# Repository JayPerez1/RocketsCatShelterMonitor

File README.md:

# Cat Shelter Monitor

Battery-powered temperature data logger to monitor temperatures and occupency in an outdoor feral cat shelter.

## Hardware (verified)
- Adafruit Feather nRF52840 Express
- DS3231 RTC + CR1220 backup
- 256KB SPI FRAM (CS = A1)
- 2x DS18B20 probes on 1-Wire (DATA = A2, external pull-up installed)
- 1S2P 18650 battery pack (not connected during bench testing)

## Firmware
- v1.0: Logging + BLE UART commands (STATUS / GETNEW / GETALL / CLEAR)

## Docs
- `docs/session-continuity.md`
- `docs/cat-shelter-chat-bootstrap.md`
- `docs/Cat_Shelter_BOM_v4.xlsx`

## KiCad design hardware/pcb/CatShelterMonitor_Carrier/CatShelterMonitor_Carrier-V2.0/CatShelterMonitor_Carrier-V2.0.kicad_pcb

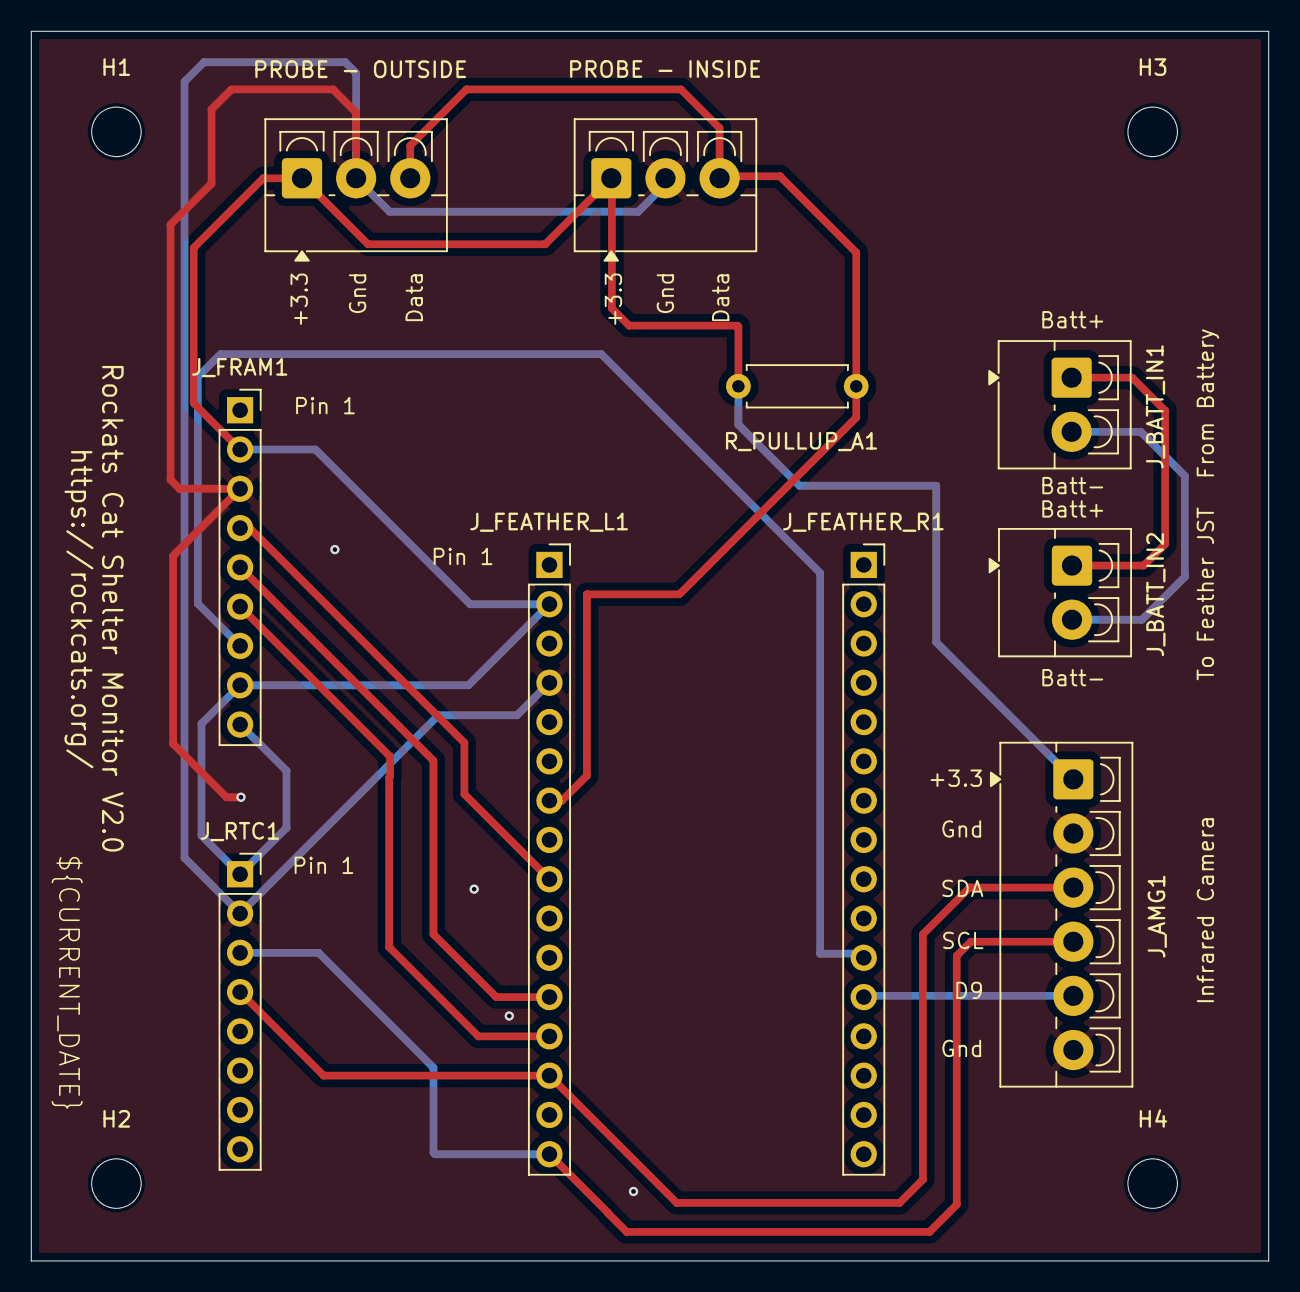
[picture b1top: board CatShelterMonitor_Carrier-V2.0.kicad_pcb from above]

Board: 2 copper layers, 80.0 x 79.5 mm, 14 parts (0 on the bottom side), 12 nets.

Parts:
H1, H2, H3, H4: MountingHole_3.2mm_M3
J_AMG1: TerminalBlock_1x06_P3.5mm; TerminalBlock_4Ucon_1x06_P3.50mm_Vertical
J_BATT_IN1, J_BATT_IN2: J_BATT_OUT; TerminalBlock_4Ucon_1x02_P3.50mm_Vertical
J_FEATHER_L1: Conn_01x16; PinSocket_1x16_P2.54mm_Vertical
J_FEATHER_R1: Conn_01x16; PinSocket_1x16_P2.54mm_Vertical
J_FRAM1: Conn_01x09; PinSocket_1x09_P2.54mm_Vertical
J_RTC1: Conn_01x08; PinSocket_1x08_P2.54mm_Vertical
PROBE - INSIDE: Conn_01x03_Socket; TerminalBlock_4Ucon_1x03_P3.50mm_Vertical
PROBE - OUTSIDE: Conn_01x03_Socket; TerminalBlock_4Ucon_1x03_P3.50mm_Vertical
R_PULLUP_A1: 4.7k; R_Axial_DIN0207_L6.3mm_D2.5mm_P7.62mm_Horizontal

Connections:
+3V3: J_AMG1.1, J_FEATHER_L1.2, J_FRAM1.2, J_FRAM1.8, J_FRAM1.9, J_RTC1.1, PROBE - INSIDE.1, PROBE - OUTSIDE.1, R_PULLUP_A1.2
/A2_1WIRE: J_FEATHER_L1.7, PROBE - INSIDE.3, PROBE - OUTSIDE.3, R_PULLUP_A1.1
/AMG_INT_D9: J_AMG1.5, J_FEATHER_R1.12
/BATT+: J_BATT_IN1.1, J_BATT_IN2.1
/BATT-: J_BATT_IN1.2, J_BATT_IN2.2
/FRAM_CS_D10: J_FEATHER_R1.11, J_FRAM1.7
/I2C_SCL: J_AMG1.4, J_FEATHER_L1.16, J_RTC1.3
/I2C_SDA: J_AMG1.3, J_FEATHER_L1.14, J_RTC1.4
/SPI_MISO: J_FEATHER_L1.12, J_FRAM1.5
/SPI_MOSI: J_FEATHER_L1.13, J_FRAM1.6
/SPI_SCK: J_FEATHER_L1.9, J_FRAM1.4
GND: J_AMG1.2, J_AMG1.6, J_FEATHER_L1.4, J_FRAM1.3, J_RTC1.2, PROBE - INSIDE.2, PROBE - OUTSIDE.2

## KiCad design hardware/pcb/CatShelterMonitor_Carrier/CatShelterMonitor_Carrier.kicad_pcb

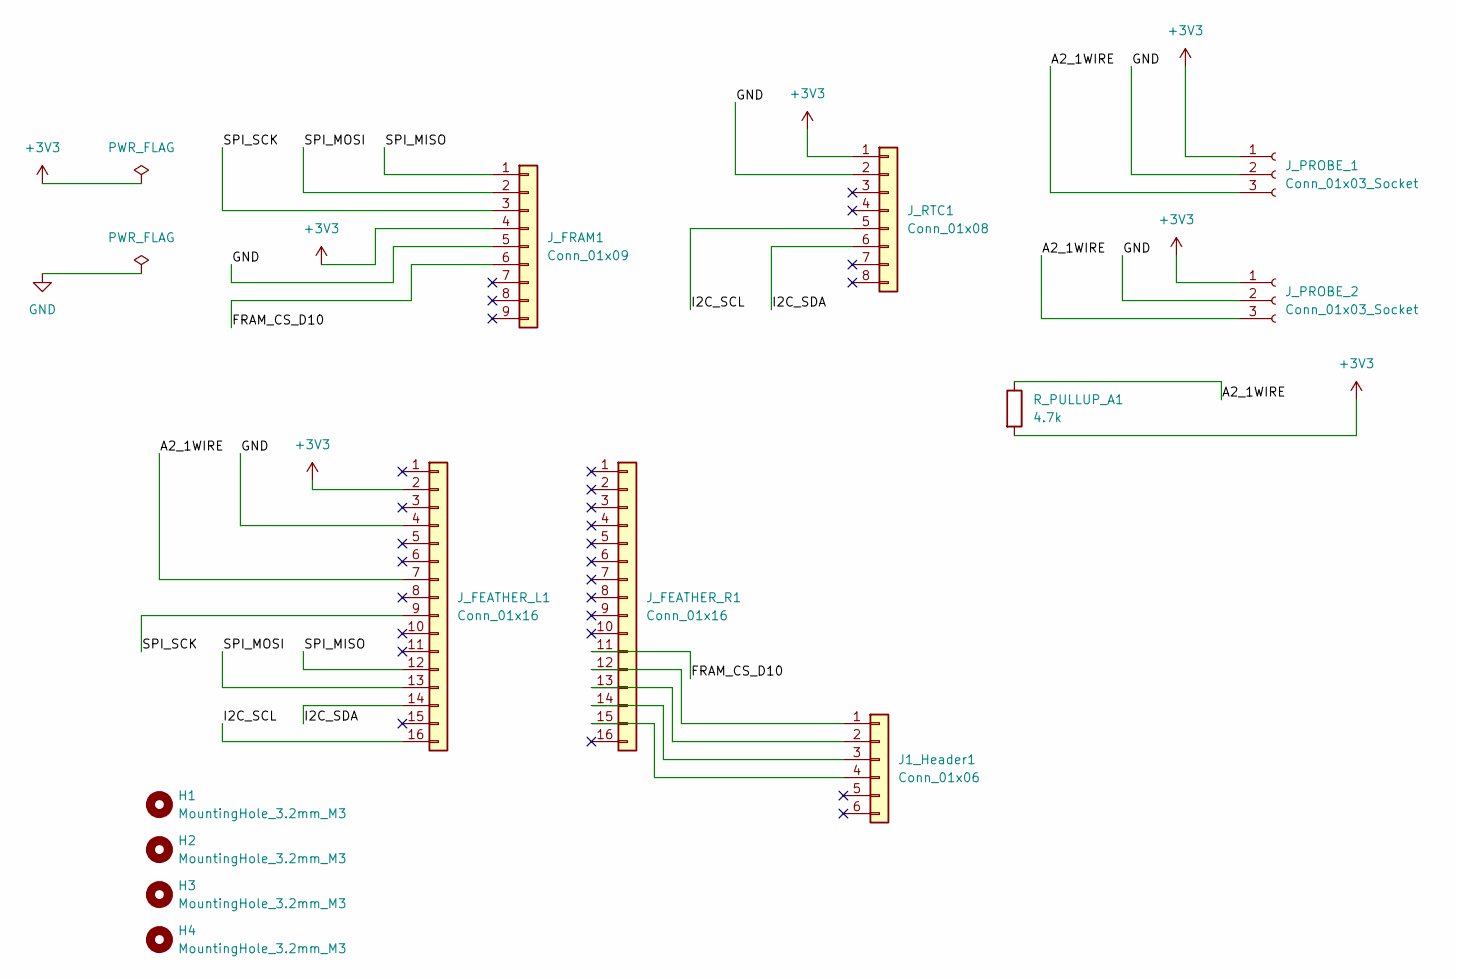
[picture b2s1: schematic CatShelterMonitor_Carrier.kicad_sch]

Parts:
H1, H2, H3, H4: MountingHole_3.2mm_M3
J1_Header1: Conn_01x06; PinSocket_1x06_P2.54mm_Vertical
J_FEATHER_L1: Conn_01x16; PinSocket_1x16_P2.54mm_Vertical
J_FEATHER_R1: Conn_01x16; PinSocket_1x16_P2.54mm_Vertical
J_FRAM1: Conn_01x09; PinSocket_1x09_P2.54mm_Vertical
J_PROBE_1, J_PROBE_2: Conn_01x03_Socket; TerminalBlock_4Ucon_1x03_P3.50mm_Vertical
J_RTC1: Conn_01x08; PinSocket_1x08_P2.54mm_Vertical
R_PULLUP_A1: 4.7k; R_Axial_DIN0207_L6.3mm_D2.5mm_P7.62mm_Horizontal

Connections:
+3V3: J_FEATHER_L1.2, J_FRAM1.4, J_PROBE_1.1, J_PROBE_2.1, J_RTC1.1, R_PULLUP_A1.2
/A2_1WIRE: J_FEATHER_L1.7, J_PROBE_1.3, J_PROBE_2.3, R_PULLUP_A1.1
/FRAM_CS_D10: J_FEATHER_R1.11, J_FRAM1.6
/I2C_SCL: J_FEATHER_L1.16, J_RTC1.5
/I2C_SDA: J_FEATHER_L1.14, J_RTC1.6
/SPI_MISO: J_FEATHER_L1.12, J_FRAM1.1
/SPI_MOSI: J_FEATHER_L1.13, J_FRAM1.2
/SPI_SCK: J_FEATHER_L1.9, J_FRAM1.3
GND: J_FEATHER_L1.4, J_FRAM1.5, J_PROBE_1.2, J_PROBE_2.2, J_RTC1.2
unnamed: J1_Header1.1, J_FEATHER_R1.12
unnamed: J1_Header1.2, J_FEATHER_R1.13
unnamed: J1_Header1.3, J_FEATHER_R1.14
unnamed: J1_Header1.4, J_FEATHER_R1.15

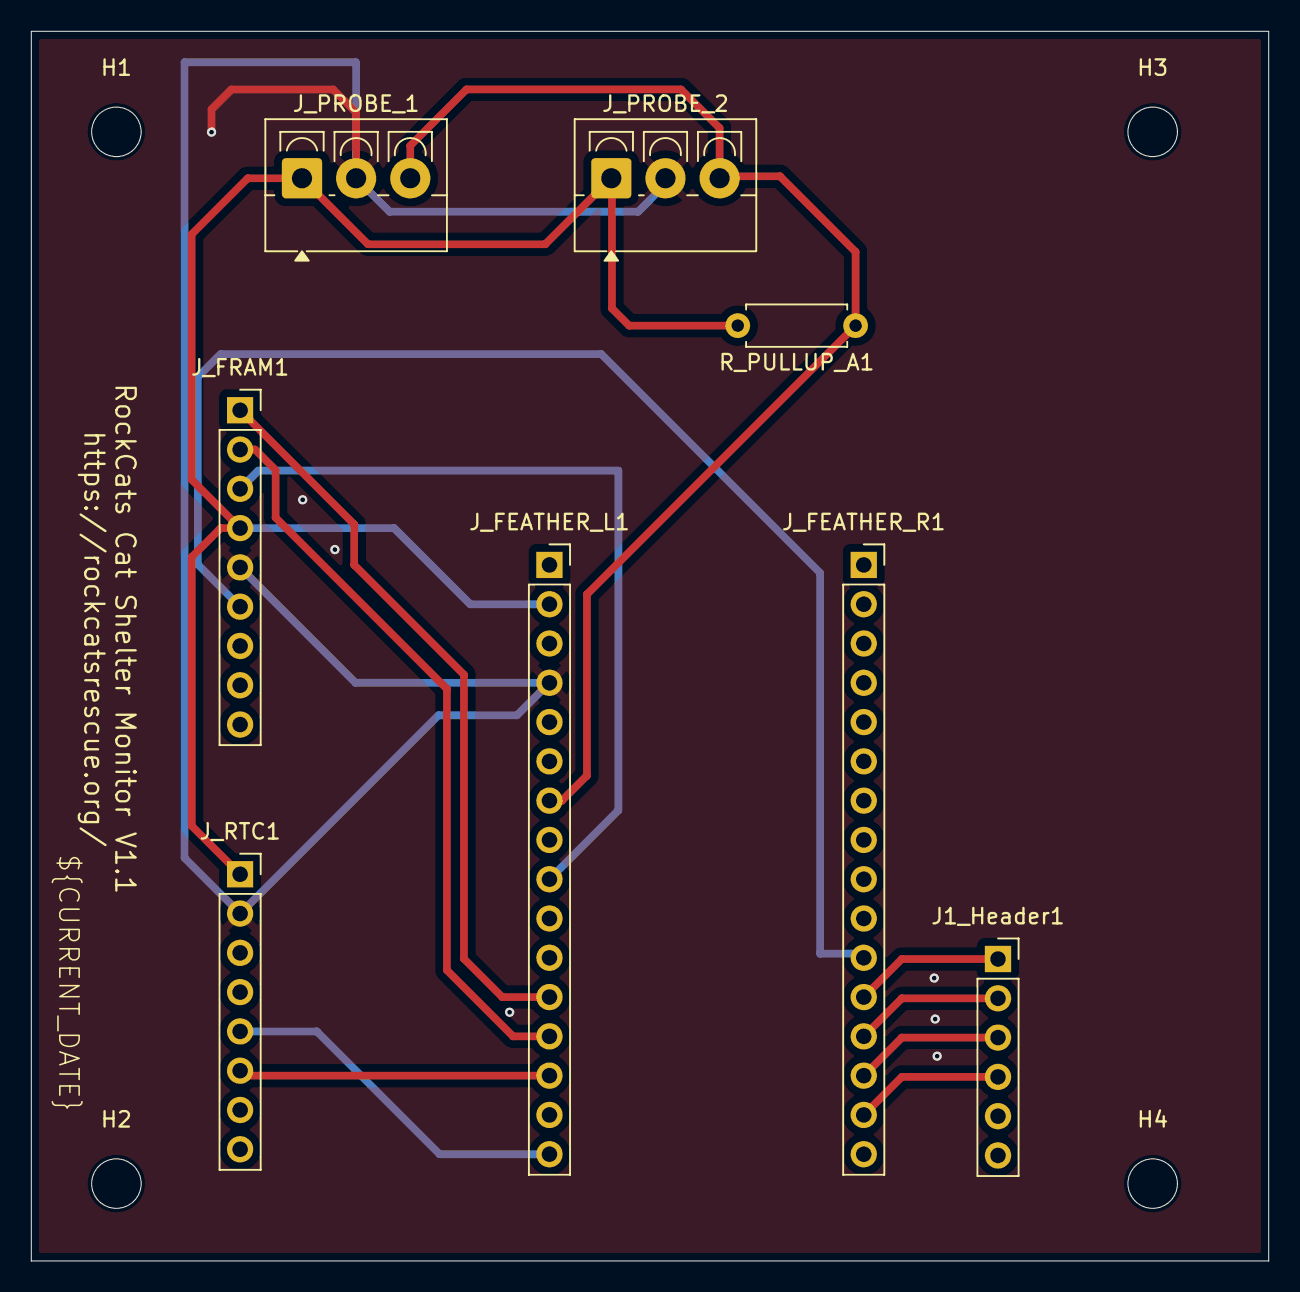
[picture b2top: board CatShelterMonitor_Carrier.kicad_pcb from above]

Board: 2 copper layers, 80.0 x 79.5 mm, 12 parts (0 on the bottom side), 13 nets.

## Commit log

2026-01-16 Baseline: hardware verified + firmware v1.0
2026-01-16 WIP: v1.1 BLE usability + diagnostics (FRAM offline, breadboard rebuild)
2026-01-16 TEMP: RAM-only logging sketch for PoC demo (no FRAM)
2026-01-16 TEMP: shorten CSV for BLE terminal compatibility (RAM demo)
2026-01-17 TEMP: RAM demo stable (RTC + 2x DS18B20 verified)
2026-01-17 Add authoritative session continuity doc (pre-FRAM reintegration)
2026-01-18 Add KiCad v1 carrier PCB project and gitignore
2026-01-18 PCB: schematic wired; expansion header added; ERC power exclusions documented
2026-01-18 Docs: update session continuity after PCB ERC cleanup
2026-01-28 Carrier PCB: Feather header spacing fixed, routing reconnected, DRC clean
    Baseline commit before board size reduction.
    Feather headers set to exact 20.32mm spacing and locked.
    All nets routed, GND pour complete, DRC clean.
2026-01-30 Resolve footprint parity errors and verify probe routing
    Corrected Schematic Parity: Updated J_PROBE_1 and J_PROBE_2 symbols to match the assigned TerminalBlock_4Ucon footprints.
    Modified Symbol Library: Updated the footprint filters in Project_Connectors.kicad_sym to allow TerminalBlock* footprints, resolving persistent DRC warnings.
    Verified Board Connectivity: Ran a full Design Rules Check (DRC) confirming zero violations and zero unconnected items across all nets.
    Synchronized Project Files: Linked schematic values and footprints to the PCB layout using the "Update PCB from Schematic" tool with re-linking enabled.
2026-01-30 Release v1.1: Finalize production files with EMI shielding and silkscreen labels
    Improvements & Changes
    Enhanced EMI Shielding: Implemented "via stitching" by adding 7 GND vias to tie top and bottom copper planes, effectively filling previously unconnected copper pockets.
    Added Identification Labels: Placed project name ("Rockets Cat Shelter Monitor") and version number (V1.1) on the top silkscreen layer for physical identification.
    Automated Versioning: Included an auto-updating date variable ${CURRENT_DATE} on the silkscreen to track fabrication timing.
    Production File Generation: Successfully plotted 11 Gerber and Drill files using Protel filename extensions for maximum manufacturer co
2026-01-30 Added Silkscreen
    Added silkscreen with project info and date.
2026-02-07 Add 18650 battery pack wiring schematic (Rev A)
2026-02-08 Add .gitignore rules for KiCad artifacts
2026-03-05 Cat Shelter: finalize field battery enclosure wiring (B+/B-, P+/P-, RUEF110 fuse, 3ft 22AWG cable)
2026-03-05 PCB RevB: add KiCad project files (carrier schematic + PCB)
2026-03-05 Cat Shelter: update BOM v4 and v1.1 firmware
2026-03-08 Add updated CatShelter documentation, BOM v2, enclosure CAD models, and PlatformIO project structure
2026-03-08 Improve .gitignore for KiCad, PlatformIO, and editor artifacts
2026-03-08 Update .gitignore to ignore KiCad backups and development artifacts
2026-03-08 Add AMG8833 and nRF52840 Feather reference datasheets
2026-03-08 Add CatShelterMonitor Carrier PCB V2.0 and RevC variants
2026-03-08 Reorganize CatShelter carrier PCB repo structure
2026-03-09 Organize hardware assets into enclosure and datasheet folders
2026-03-11 Fix firmware folder structure for CatShelterLogger_v1_0
2026-03-11 Add firmware README documentation
